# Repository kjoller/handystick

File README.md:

HandyStick is yet another small development board with an AtmegaX8 (Atmega88,
Atmega168, Atmega328). The board is targeted towards use with vUsb, a software
implemented USB stack.

It is cheap to manufacture, fitting two on a cheap 5x5cm 2-layer pcb, and using
easy-to-source parts.

Possible uses:

* Using projects like USBAspLoader, you can get a USB programmable AVR board for less than $3 in parts.
* You can use this for USB HID-devices, such as joysticks, gamepads or even a full-featured MAME cabinet
* USB dataloggers
* For more ideas, see the vUSB web site.

The first panel is panelised with mouse bites (tab routing), so not all PCB
services will take it. I have ordered the first batch on DirtyPCBs. 

(For added vendor flexibility, it would be wise to panelize it using only
silkscreen seperators. with just silkscreen, 5 should fit easily on a 5x10cm
board, making it even cheaper.)

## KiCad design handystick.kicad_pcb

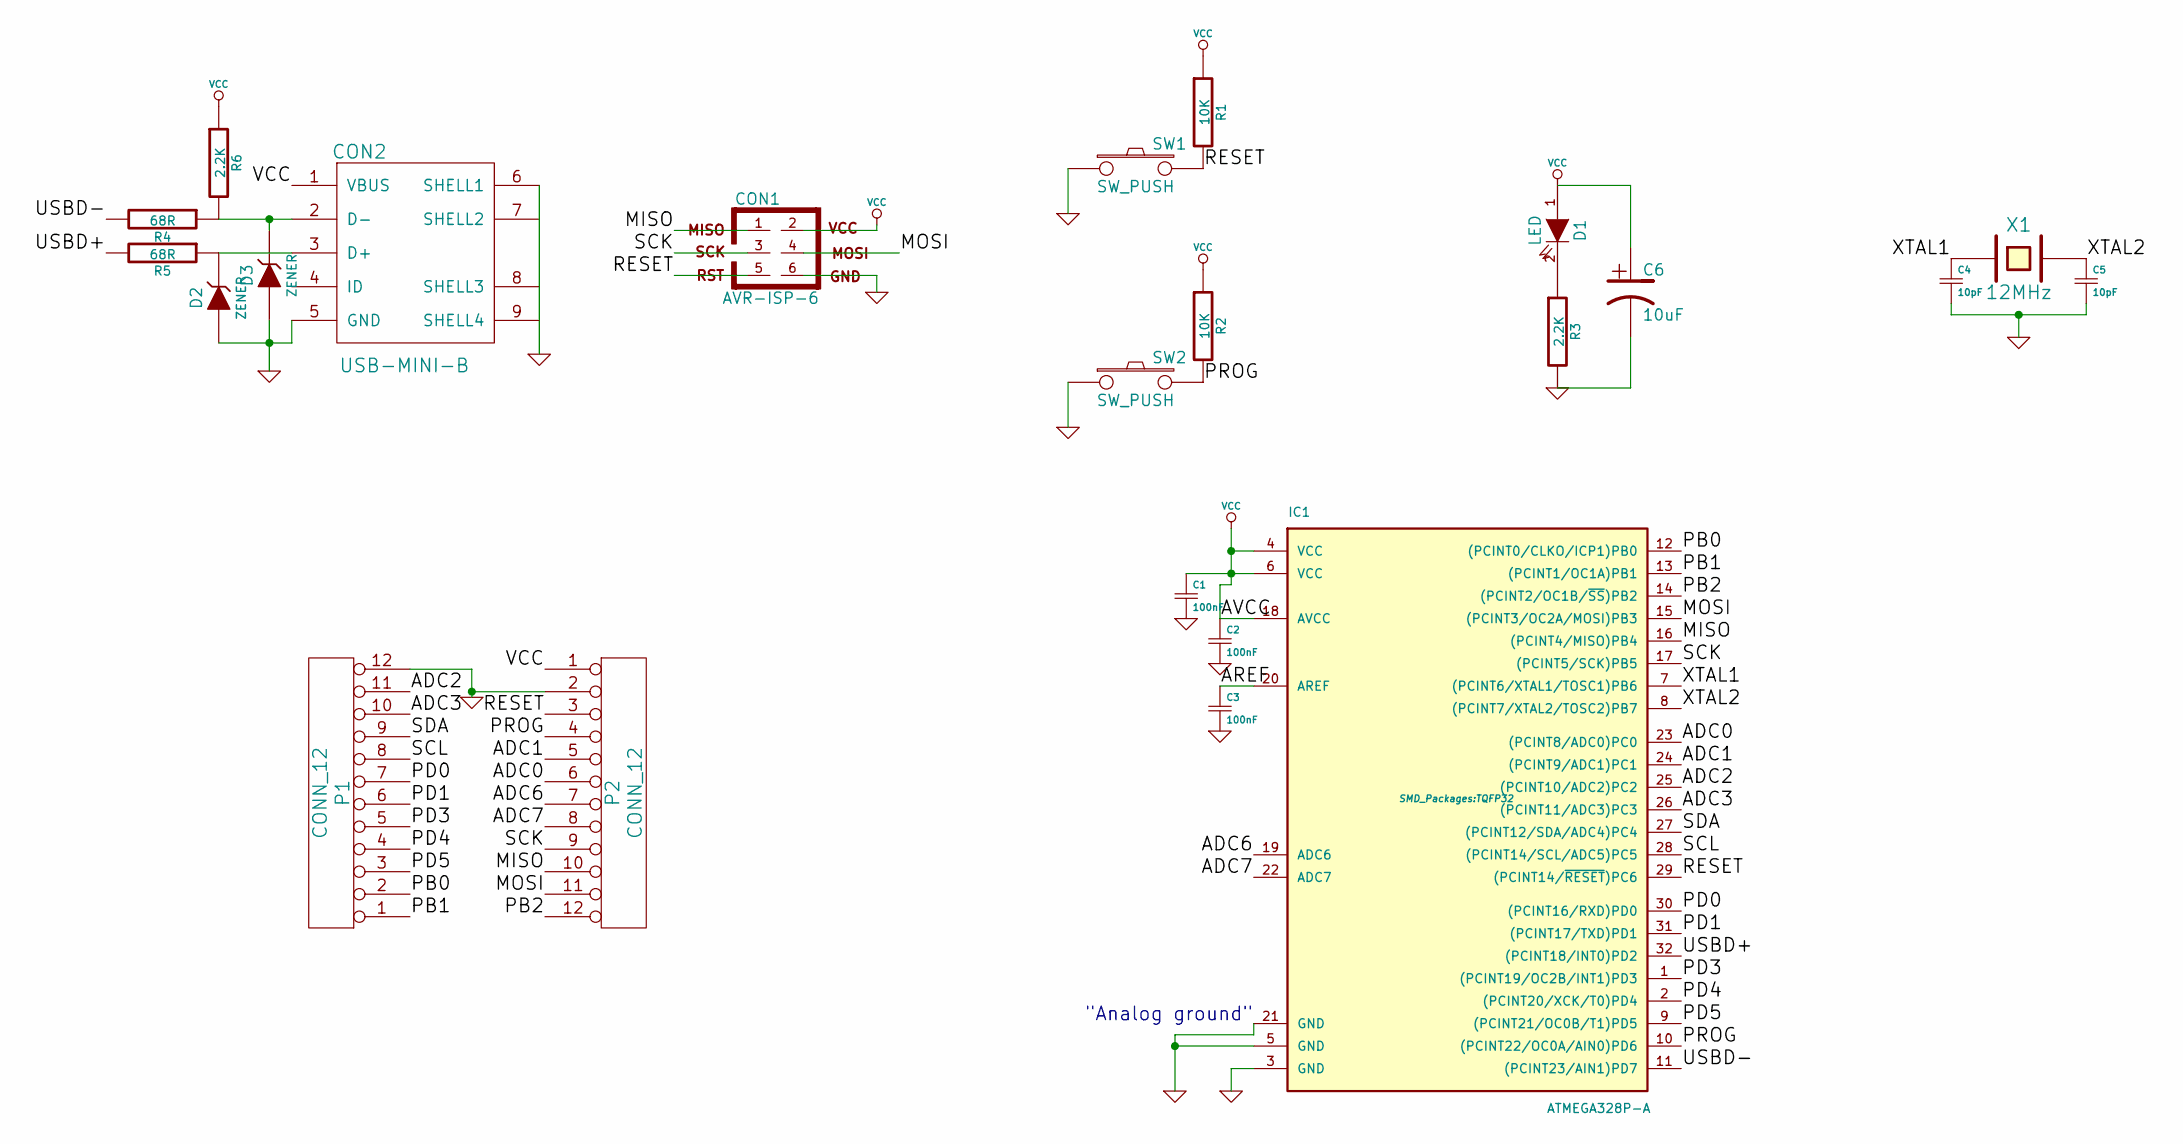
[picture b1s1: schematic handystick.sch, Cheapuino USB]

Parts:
C1, C2, C3: 100nF; SMD_0603
C4, C5: 10pF; c_0805
C6: 10uF
CON1: AVR-ISP-6; Pin_Header_Straight_2x03
CON2: USB-MINI-B; USB_Micro_B_SMD+DIP_long
D1: LED; SMD_0805
D2, D3: ZENER; Diode-MiniMELF_Handsoldering
IC1: ATMEGA328P-A; TQFP32
P1, P2: CONN_12; Pinrow_12p_oval
R1, R2: 10K; SMD_0603
R3, R6: 2.2K; SMD_0603
R4, R5: 68R; SMD_0805
SW1, SW2: SW_PUSH; 3x6_smd_button
X1: 12MHz; crystal_5032_2p

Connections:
/ADC0: IC1.23 ((PCINT8/ADC0)PC0), P2.6
/ADC1: IC1.24 ((PCINT9/ADC1)PC1), P2.5
/ADC2: IC1.25 ((PCINT10/ADC2)PC2), P1.11
/ADC3: IC1.26 ((PCINT11/ADC3)PC3), P1.10
/ADC6: IC1.19 (ADC6), P2.7
/ADC7: IC1.22 (ADC7), P2.8
/AREF: C3.1, IC1.20 (AREF)
/MISO: CON1.1, IC1.16 ((PCINT4/MISO)PB4), P2.10
/MOSI: CON1.4, IC1.15 ((PCINT3/OC2A/MOSI)PB3), P2.11
/PB0: IC1.12 ((PCINT0/CLKO/ICP1)PB0), P1.2
/PB1: IC1.13 ((PCINT1/OC1A)PB1), P1.1
/PB2: IC1.14 ((PCINT2/OC1B/~SS~)PB2), P2.12
/PD0: IC1.30 ((PCINT16/RXD)PD0), P1.7
/PD1: IC1.31 ((PCINT17/TXD)PD1), P1.6
/PD3: IC1.1 ((PCINT19/OC2B/INT1)PD3), P1.5
/PD4: IC1.2 ((PCINT20/XCK/T0)PD4), P1.4
/PD5: IC1.9 ((PCINT21/OC0B/T1)PD5), P1.3
/PROG: IC1.10 ((PCINT22/OC0A/AIN0)PD6), P2.4, R2.2, SW2.2
/RESET: CON1.5, IC1.29 ((PCINT14/~RESET~)PC6), P2.3, R1.2, SW1.2
/SCK: CON1.3, IC1.17 ((PCINT5/SCK)PB5), P2.9
/SCL: IC1.28 ((PCINT14/SCL/ADC5)PC5), P1.8
/SDA: IC1.27 ((PCINT12/SDA/ADC4)PC4), P1.9
/USBD+: IC1.32 ((PCINT18/INT0)PD2), R5.2
/USBD-: IC1.11 ((PCINT23/AIN1)PD7), R4.2
/XTAL1: C4.1, IC1.7 ((PCINT6/XTAL1/TOSC1)PB6), X1.1
/XTAL2: C5.1, IC1.8 ((PCINT7/XTAL2/TOSC2)PB7), X1.2
GND: C1.2, C2.2, C3.2, C4.2, C5.2, C6.2, CON1.6, CON2.5 (GND), CON2.6 (SHELL1), CON2.7 (SHELL2), CON2.8 (SHELL3), CON2.9 (SHELL4), D2.1 (A), D3.1 (A), IC1.3 (GND), IC1.5 (GND), IC1.21 (GND), P1.12, P2.2, R3.2, SW1.1, SW2.1; also elsewhere on the board
unnamed: CON2.2 (D-), D3.2 (K), R4.1, R6.2
unnamed: CON2.3 (D+), D2.2 (K), R5.1
unnamed: D1.2 (K), R3.1
VCC: C1.1, C2.1, C6.1, CON1.2, CON2.1 (VBUS), D1.1 (A), IC1.4 (VCC), IC1.6 (VCC), IC1.18 (AVCC), P2.1, R1.1, R2.1, R6.1

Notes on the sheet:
"Analog ground"

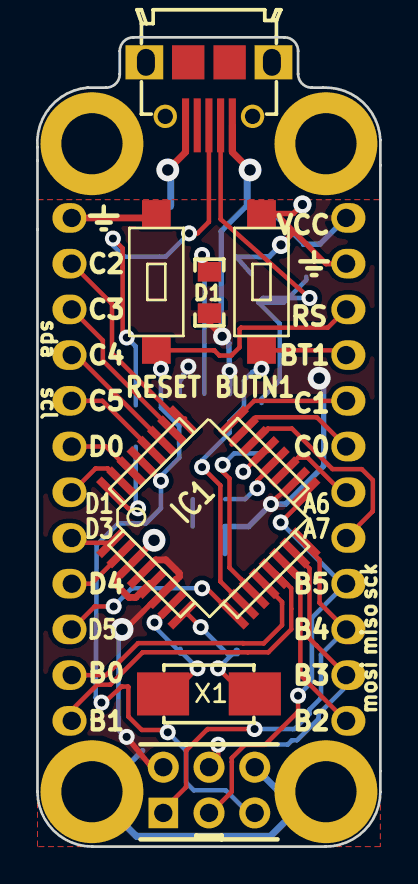
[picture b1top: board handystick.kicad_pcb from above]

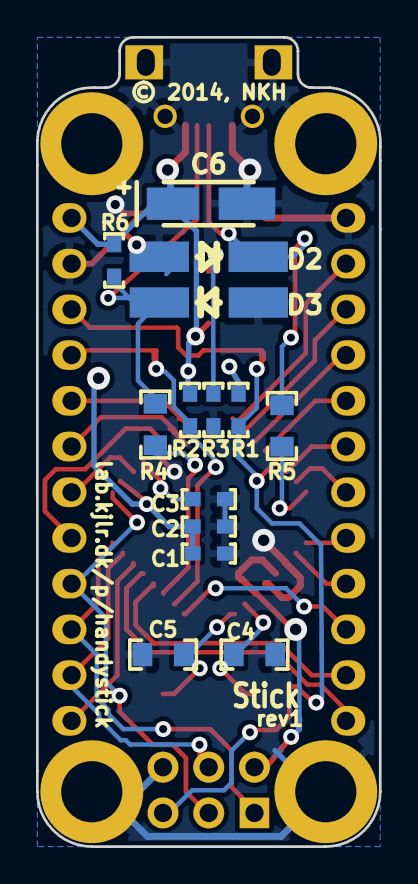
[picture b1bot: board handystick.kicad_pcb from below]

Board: 2 copper layers, 19.1 x 45.0 mm, 27 parts (14 on the bottom side), 31 nets.

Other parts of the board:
1PIN, 1PIN#2, 1PIN#3, 1PIN#4: P***; M3_mounting_hole

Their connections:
GND: 1PIN.1, 1PIN#2.1, 1PIN#3.1, 1PIN#4.1; also elsewhere on the board

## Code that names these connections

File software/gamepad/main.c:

#include <avr/io.h>
#include <avr/interrupt.h>
#include <avr/pgmspace.h>
#include <avr/wdt.h>
#include "usbdrv.h"

#include <util/delay.h>

static void hardwareInit(void)
{
//    PORTB = 0xff;   /* activate all pull-ups */
    DDRB = 0b00100000;       /* all pins input */
//    PORTC = 0xff;   /* activate all pull-ups */
    DDRC = 0;       /* all pins input */
    DDRD =  0b10000100;   /* 0000 0111 bin: all pins input except USB (-> USB reset) */
    DDRD = 0x02;    /* 0000 0010 bin: remove USB reset condition */
}

uchar sentMask;
uchar readMask;

/* ------------------------------------------------------------------------- */
/* ----------------------------- USB interface ----------------------------- */
/* ------------------------------------------------------------------------- */

static uchar    idleRate;           /* in 4 ms units */

const PROGMEM char usbHidReportDescriptor[42] = {   /* USB report descriptor */
    0x05, 0x01,                    // USAGE_PAGE (Generic Desktop)
    0x09, 0x05,                    // USAGE (Keyboard)
    0xa1, 0x01,                    // COLLECTION (Application)
    0xa1, 0x00,                    //  COLLECTION (Physical)
    0x05, 0x09,                    //   USAGE_PAGE (Button)
    0x19, 0x01,                    //   USAGE_MINIMUM (Button 1)
    0x29, 0x04,                    //   USAGE_MAXIMUM (Button 4)
    0x15, 0x00,                    //   LOGICAL_MINIMUM (0)
    0x25, 0x01,                    //   LOGICAL_MAXIMUM (1)
    0x95, 0x04,                    //   REPORT_COUNT (4)
    0x75, 0x01,                    //   REPORT_SIZE (1)
    0x81, 0x02,                    //   INPUT (Data,Var,Abs)

    0x05, 0x01,                    //   USAGE_PAGE (Generic Desktop)
    0x09, 0x30,                    //   USAGE(X)
    0x09, 0x31,                    //   USAGE(Y)
    0x15, 0xff,                    //   LOGICAL_MINIMUM (-1)
    0x25, 0x01,                    //   LOGICAL_MAXIMUM (1)
    0x95, 0x02,                    //   REPORT_COUNT (2)
    0x75, 0x02,                    //   REPORT_SIZE (2)
    0x81, 0x02,                    //   INPUT (Data,Var,Abs)
    0xc0,                          // END_COLLECTION
    0xc0                           // END_COLLECTION
};

typedef struct {
   uchar buttonMask;
} report_t;

static report_t reportBuffer;
static uchar    idleRate;



usbMsgLen_t usbFunctionSetup(uchar data[8]) {
    usbRequest_t *rq = (void *)data;

    // The following requests are never used. But since they are required by
    // the specification, we implement them in this example.
    if((rq->bmRequestType & USBRQ_TYPE_MASK) == USBRQ_TYPE_CLASS) {
        if(rq->bRequest == USBRQ_HID_GET_REPORT) {  
            // wValue: ReportType (highbyte), ReportID (lowbyte)
            usbMsgPtr = (void *)&reportBuffer; // we only have this one
            return sizeof(reportBuffer);
        } else if(rq->bRequest == USBRQ_HID_GET_IDLE) {
            usbMsgPtr = &idleRate;
            return 1;
        } else if(rq->bRequest == USBRQ_HID_SET_IDLE) {
            idleRate = rq->wValue.bytes[1];
        }
    }
    
    return 0; // by default don't return any data
}


/* ------------------------------------------------------------------------- */


// Interrupt for Port D (Where the arrows are)
ISR(PCINT1_vect) {
    readMask &= 0b00001111;
    // Right or left?
    if (!(PINC & (1<<PC5))) {       // If left is pushed set bit 6 and 
		readMask |= (3<<4);      // 7 to '11' (-1)
	} else if (!(PINC & (1<<PC3))) { // If right is pushed, set bit 6 and
		readMask |= (1<<4);      // 7 to '01' (1)
        readMask &= ~(1<<5);
	}                            // bits to '00' (0) - neutral.

	// Up or down?
    if (!(PINC & (1<<PC4))) {        // If up
		readMask |= (3<<6);
	} else if (!(PINC & (1<<PC2))) {  // If down
		readMask |= (1<<6);
        readMask &= ~(1<<7);
	}
}

// Interrupt for Port B (Where the buttons are)
ISR(PCINT0_vect) {
    readMask &= 0b11110000;
	if (!(PINB & (1<<PB3))) readMask |= 1;
	if (!(PINB & (1<<PB2))) readMask |= 1<<1;
	if (!(PINB & (1<<PB4))) readMask |= 1<<2;
	if (!(PINB & (1<<PB1))) readMask |= 1<<3;
}

void initButtonInterrupts(void) {
	PCICR |= (1<<PCIE1) | (1<<PCIE0);
	PCMSK1 |= (1<<PC5) | (1<<PC4) | (1<<PC3) | (1<<PC2);
	PCMSK0 |= (1<<PB1) | (1<<PB2) | (1<<PB3) | (1<<PB4);
}

int	main(void)
{
	uchar i;
	wdt_enable(WDTO_2S);
    hardwareInit();
    initButtonInterrupts();
	usbInit();
    usbDeviceDisconnect(); // enforce re-enumeration
    for(i = 0; i<250; i++) { // wait 500 ms
        wdt_reset(); // keep the watchdog happy
        _delay_ms(2);
    }
    usbDeviceConnect();

	sei();
	while(1) {
		wdt_reset();
        _delay_ms(20);
		usbPoll();
		
        if ((reportBuffer.buttonMask!=readMask)&(usbInterruptIsReady())){
            reportBuffer.buttonMask = readMask;
            usbSetInterrupt((void *)&reportBuffer, sizeof(reportBuffer));
			
        }
	}
	return 0;
}

/* ------------------------------------------------------------------------- */

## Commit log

2014-08-21 Cleaned up gamepad example
2014-09-19 cleaned up tree, added hex files for 328p and 88pa

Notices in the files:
handystick.kicad_pcb:
© 2014, NKH
